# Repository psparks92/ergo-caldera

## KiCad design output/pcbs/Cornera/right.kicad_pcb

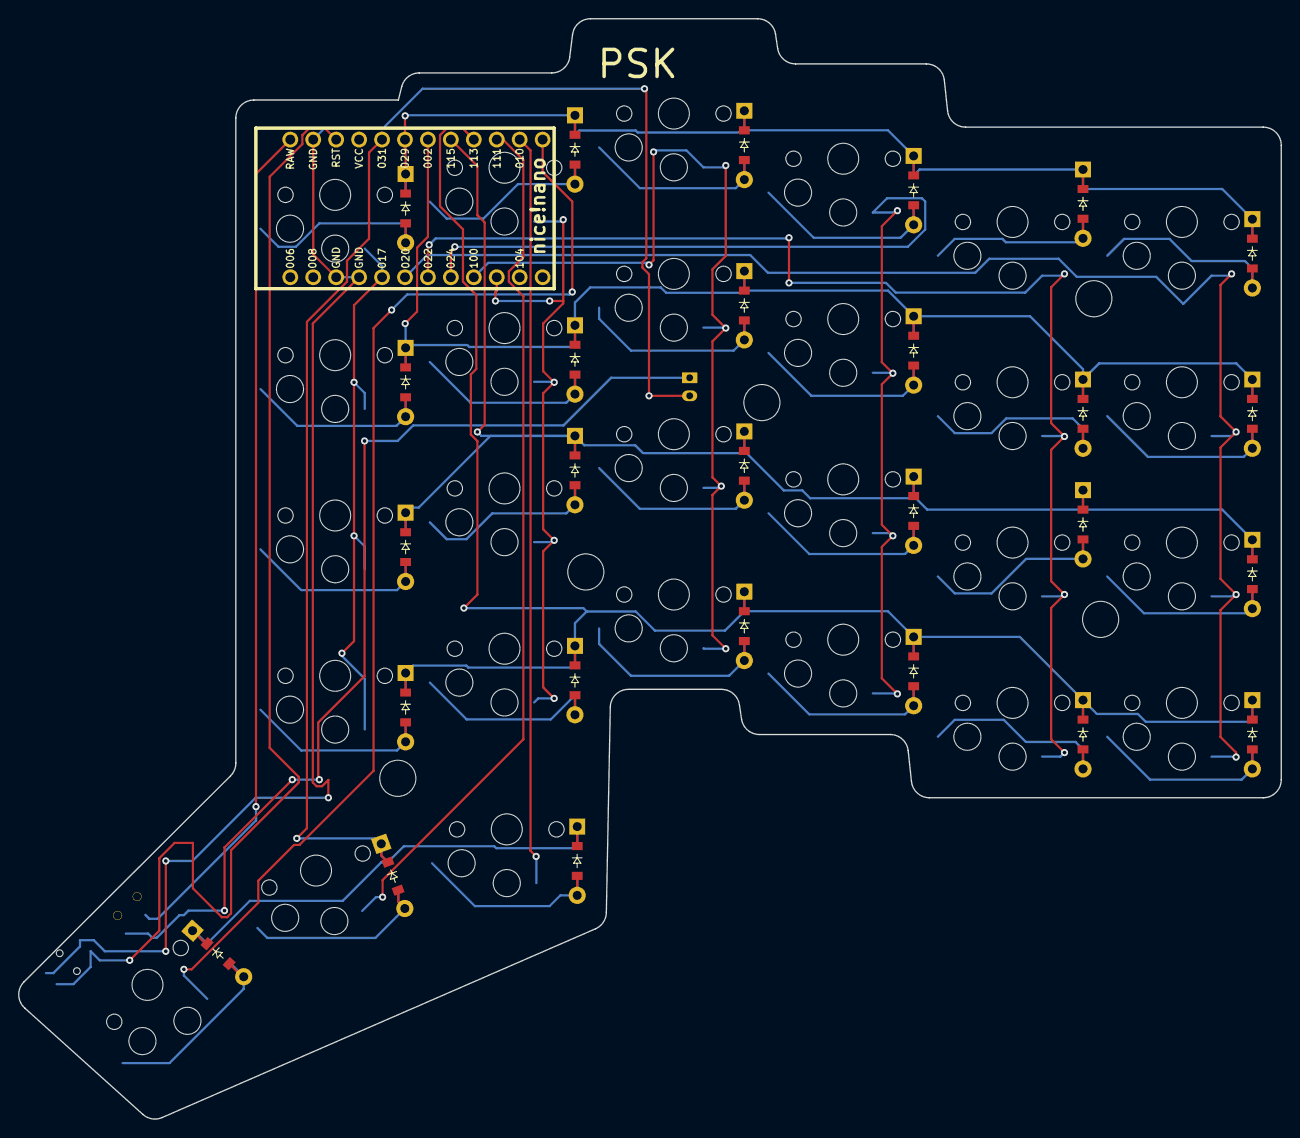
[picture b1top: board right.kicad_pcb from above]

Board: 2 copper layers, 139.8 x 121.8 mm, 58 parts (0 on the bottom side), 45 nets.

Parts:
B1: Panasonic_EVQPUL_EVQPUC
D1, D2, D3, D4, D5, D6, D7, D8, D9, D10, D11, D12, D13, D14, D15, D16, D17, D18, D19, D20, D21, D22, D23, D24, D25, D26, D27: ComboDiode
JST1: JST_PH_S2B-PH-K_02x2.00mm_Angled
MCU1: nice_nano
S1, S2, S3, S4, S5, S6, S7, S8, S9, S10, S11, S12, S13, S14, S15, S16, S17, S18, S19, S20, S21, S22, S23, S24, S25, S26, S27: PG1350
T1: SPDT_C128955

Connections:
GND: B1.1, JST1.2, MCU1.3, MCU1.4, MCU1.23
P002: D3.1, D6.1, D9.1, D15.1, D26.1, D27.1, MCU1.18
P009: MCU1.13, S27.1
P010: MCU1.14, S25.1
P011: MCU1.10, S17.1, S18.1, S19.1, S20.1
P017: MCU1.5, S21.1, S22.1, S23.1, S24.1
P020: MCU1.6, S1.1, S2.1, S3.1, S4.1
P022: MCU1.7, S5.1, S6.1, S7.1, S8.1
P024: MCU1.8, S9.1, S10.1, S11.1, S12.1
P029: D4.1, D10.1, D13.1, D22.1, D24.1, D25.1, MCU1.19
P031: D18.1, D19.1, D20.1, MCU1.20
P100: MCU1.9, S13.1, S14.1, S15.1, S16.1
P111: MCU1.15, S26.1
P113: D1.1, D5.1, D7.1, D11.1, D14.1, D16.1, MCU1.16
P115: D2.1, D8.1, D12.1, D17.1, D21.1, D23.1, MCU1.17
RAW: MCU1.24, T1.2
RST: B1.2, MCU1.22
mirror_far_thumb: D20.2, S27.2
mirror_fifth_bottom: D23.2, S18.2
mirror_fifth_home: D15.2, S19.2
mirror_fifth_mod: D14.2, S17.2
mirror_fifth_top: D24.2, S20.2
mirror_first_bottom: D2.2, S2.2
mirror_first_home: D3.2, S3.2
mirror_first_mod: D1.2, S1.2
mirror_first_top: D4.2, S4.2
mirror_fourth_bottom: D12.2, S14.2
mirror_fourth_home: D27.2, S15.2
mirror_fourth_mod: D11.2, S13.2
mirror_fourth_top: D13.2, S16.2
mirror_home_thumb: D19.2, S26.2
mirror_near_thumb: D18.2, S25.2
mirror_second_bottom: D21.2, S6.2
mirror_second_home: D6.2, S7.2
mirror_second_mod: D5.2, S5.2
mirror_second_top: D22.2, S8.2
mirror_sixth_bottom: D17.2, S22.2
mirror_sixth_home: D26.2, S23.2
mirror_sixth_mod: D16.2, S21.2
mirror_sixth_top: D25.2, S24.2
mirror_third_bottom: D8.2, S10.2
mirror_third_home: D9.2, S11.2
mirror_third_mod: D7.2, S9.2
mirror_third_top: D10.2, S12.2
pos: JST1.1, T1.1

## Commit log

2024-12-26 init, 4x6 + 3 format and not well connected left pcb
2024-12-26 Removing autosave right pcb, locks and stuff I guess
2024-12-26 gitignore
2024-12-26 clean slate, regenerated without trash routes
2024-12-27 routed left, removed top left mounting hole from left and right and yaml
2024-12-27 wip routing right board
2024-12-27 routed left and right, DRC passed
2024-12-27 generated gerber files, sent off for fab
2025-01-07 stls
